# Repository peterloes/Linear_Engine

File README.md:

# Linear Actuator

A standalone Platform for Animal Manipulation 

This is the firmware for the LinearA_2017 (linear servo, i.e. stepper motor with spindle)
and project Servo_2015 (standard PWM servo).
Setup and control of the Actuator is done
via 3 keys, and, for selecting the two end positions, also via two external
inputs, please see below.  The firmware supports soft-start, i.e. the Actuator
speed will be ramped-up during the start phase.

Supported:
- Nanotec SMC11-2 Leistungsendstufe
- Nanotec Linear Aktuator L2018S0604-T3,5x1

The linear setup procedure consists of 4 steps:
- Adjust end position 1.  A linear actuator
  doesn't know about its absolute position, therefore it first moves to
  to its physical start position (near the motor) after power-up.  From
  that, position 1 can be adjusted.
- Adjust end position 2.  This is the opposite end position to position 1.
- Adjust actuator speed.  The actuator permanently moves between the two end
  points.  The speed can be adjusted via S1 and S2.
- Asserting S3 the 4th time stores the servo parameters into FLASH and
  returns to normal operation.

Prototype: Feeder

https://github.com/peterloes/Linear_Engine/blob/master/Getting_Started_Tutorial/1_poster_overview.pdf

Mainboard:

https://github.com/peterloes/MOMO

Manufacture:

https://github.com/peterloes/Linear_Engine/blob/master/Getting_Started_Tutorial/3_Supplier.txt

The standalone Linear Actuator features EFM32 ...the world´s most energy friendly microcontrollers

ARM Cortex-M3 EFM32G230F128

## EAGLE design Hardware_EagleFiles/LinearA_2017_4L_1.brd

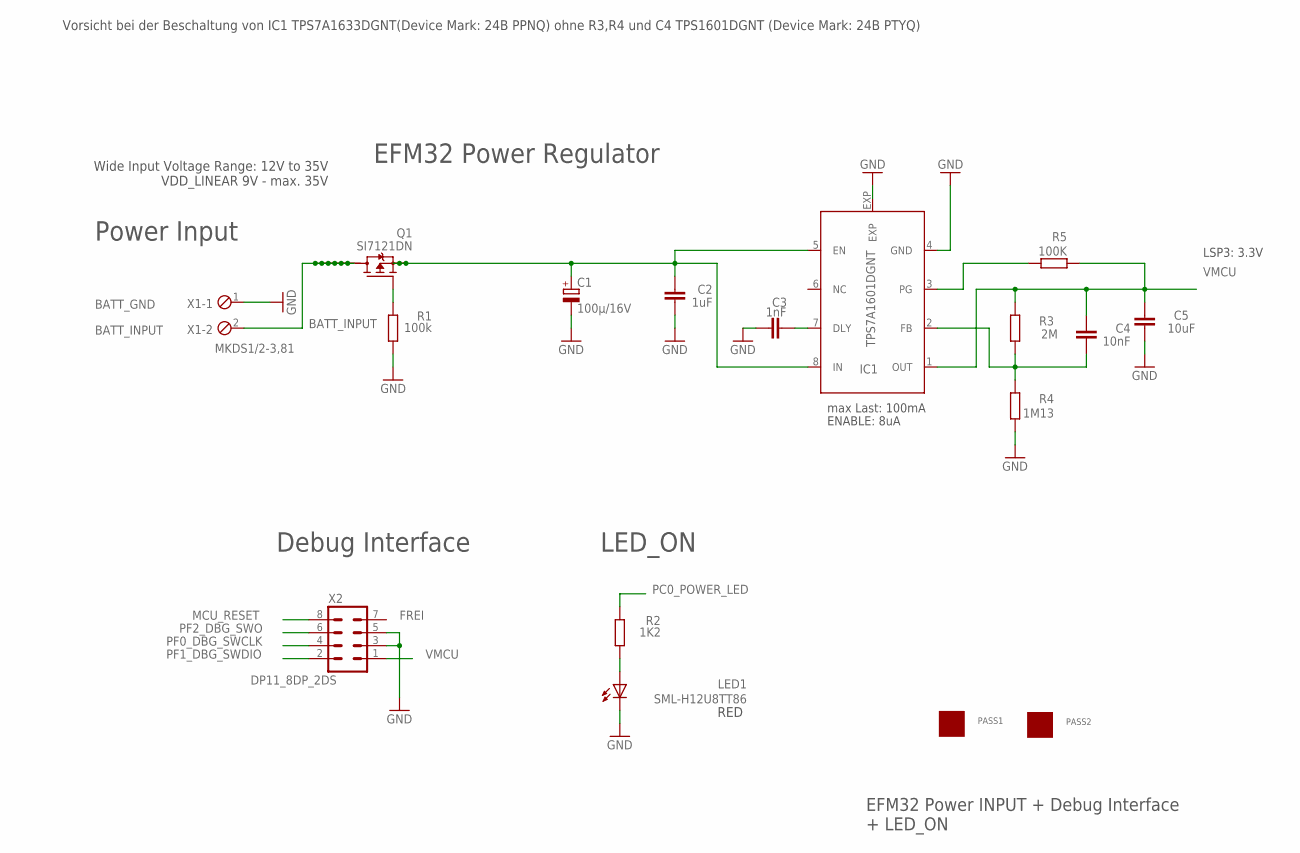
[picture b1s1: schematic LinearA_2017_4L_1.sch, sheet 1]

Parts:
C1: 100µ/16V; PANASONIC_E
C2: 1uF; C0603
C3: 1nF; C0603
C4: 10nF; C0603
C5: 10uF; C1206
IC1: TPS7A1601DGNT; DGN_S-PDSO-G8-EXP
LED1: SML-H12U8TT86; CHIPLED_0805
PASS1, PASS2: ROUND_1MM1.5; ROUND2_1.5MM
Q1: SI7121DN; TRANSISTOR-FET_1212-8S
R1: 100k; R0805
R2: 1K2; R0805
R3: 2M; R0805
R4: 1M13; R0805
R5: 100K; R0805
X1: MKDS1/2-3,81; 2POL381
X2: DP11_8DP_2DS; DP11_8DP-2DS

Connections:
BATT_INPUT: Q1.5 (D), Q1.6 (D), Q1.7 (D), Q1.8 (D), Q1.9 (D), Q1.10 (D), Q1.11 (D), X1.2; also elsewhere on the board
GND: C1.-, C2.1, C3.1, C5.1, IC1.4 (GND), IC1.EXP, LED1.C, R1.1, R4.1, X1.1, X2.3, X2.5; also elsewhere on the board
MCU_RESET: X2.8; also elsewhere on the board
unnamed: C1.+, C2.2, IC1.5 (EN), IC1.8 (IN), Q1.1 (S), Q1.2 (S), Q1.3 (S)
unnamed: C3.2, IC1.7 (DLY)
unnamed: C4.1, IC1.2 (FB), R3.1, R4.2
unnamed: IC1.3 (PG), R5.2
unnamed: Q1.4 (G), R1.2
unnamed: LED1.A, R2.2
PC0_POWER_LED: R2.1; also elsewhere on the board
PF0_DBG_SWCLK: X2.4; also elsewhere on the board
PF1_DBG_SWDIO: X2.2; also elsewhere on the board
PF2_DBG_SWO: X2.6; also elsewhere on the board
VMCU: C4.2, C5.2, IC1.1 (OUT), R3.2, R5.1, X2.1; also elsewhere on the board

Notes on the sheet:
BATT_GND
Wide Input Voltage Range: 12V to 35V VDD_LINEAR 9V - max. 35V
BATT_INPUT
EFM32 Power INPUT + Debug Interface + LED_ON
ENABLE: 8uA
Power Input
max Last: 100mA
LSP3: 3.3V
EFM32 Power Regulator
Debug Interface
LED_ON
FREI
Vorsicht bei der Beschaltung von IC1 TPS7A1633DGNT(Device Mark: 24B PPNQ) ohne R3,R4 und C4 TPS1601DGNT (Device Mark: 24B PTYQ)
RED

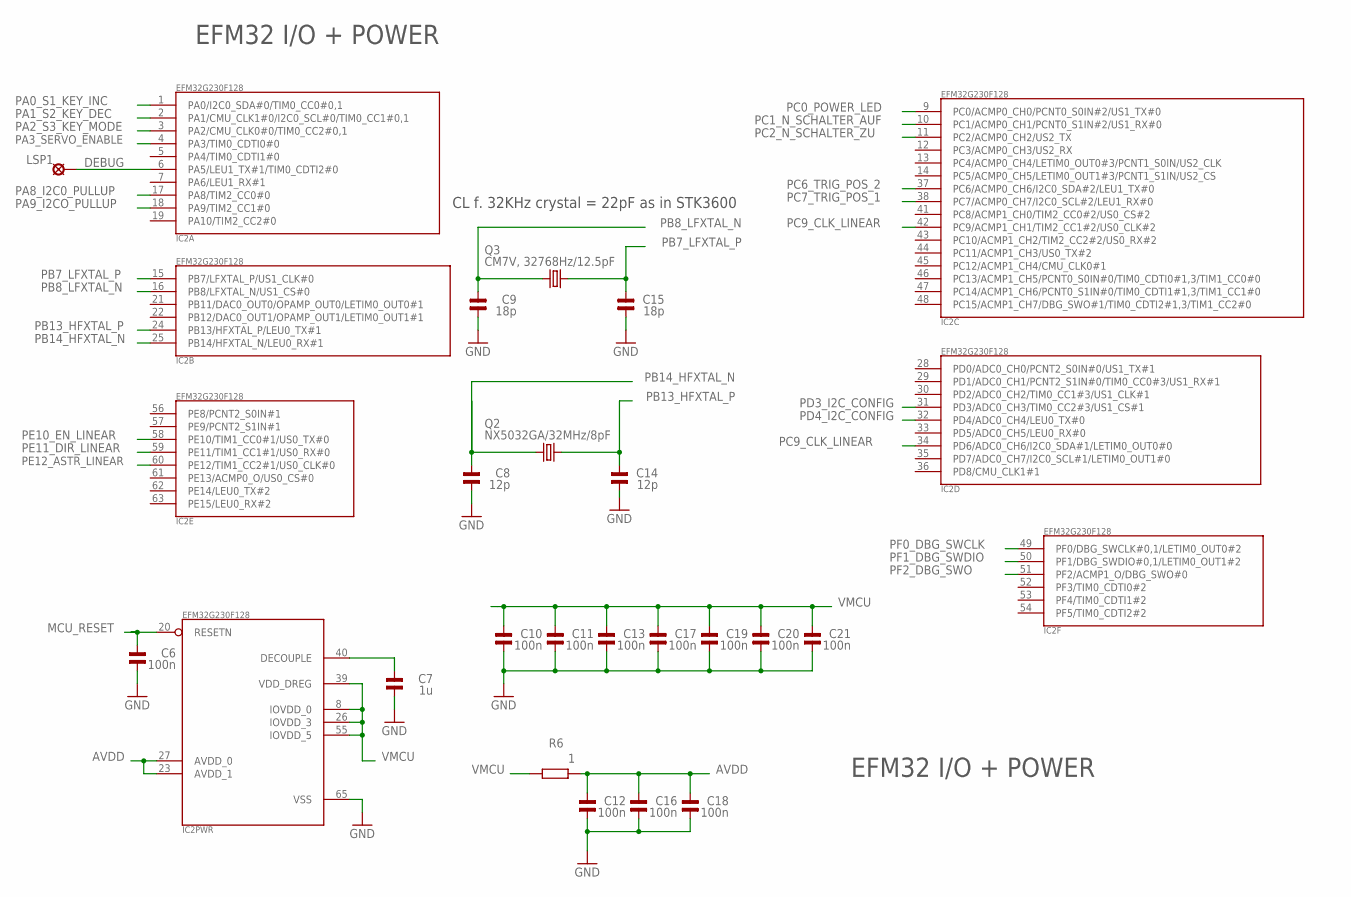
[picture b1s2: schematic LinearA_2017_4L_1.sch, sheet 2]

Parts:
C6, C10, C11, C12, C13, C16, C17, C18, C19, C20, C21: 100n; 0805
C7: 1u; 0805
C8, C14: 12p; 0805
C9, C15: 18p; 0805
IC2: EFM32G230F128; QFN64
LSP1: (n.b.)LSP10; LSP10
Q2: NX5032GA/32MHz/8pF; CRYSTAL2P5.0X3.2
Q3: CM7V, 32768Hz/12.5pF; CRYSTAL2P3.2X1.5
R6: 1; R0805

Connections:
AVDD: C12.2, C16.2, C18.2, IC2.23 (AVDD_1), IC2.27 (AVDD_0), R6.2
DEBUG: IC2.6 (PA5/LEU1_TX#1/TIM0_CDTI2#0), LSP1.MP
GND: C6.1, C7.1, C8.1, C9.1, C10.1, C11.1, C12.1, C13.1, C14.1, C15.1, C16.1, C17.1, C18.1, C19.1, C20.1, C21.1, IC2.65 (VSS); also elsewhere on the board
MCU_RESET: C6.2, IC2.20 (RESETN); also elsewhere on the board
unnamed: C7.2, IC2.40 (DECOUPLE)
PA0_S1_KEY_INC: IC2.1 (PA0/I2C0_SDA#0/TIM0_CC0#0,1); also elsewhere on the board
PA1_S2_KEY_DEC: IC2.2 (PA1/CMU_CLK1#0/I2C0_SCL#0/TIM0_CC1#0,1); also elsewhere on the board
PA2_S3_KEY_MODE: IC2.3 (PA2/CMU_CLK0#0/TIM0_CC2#0,1); also elsewhere on the board
PA3_SERVO_ENABLE: IC2.4 (PA3/TIM0_CDTI0#0); also elsewhere on the board
PA8_I2C0_PULLUP: IC2.17 (PA8/TIM2_CC0#0); also elsewhere on the board
PA9_I2CO_PULLUP: IC2.18 (PA9/TIM2_CC1#0); also elsewhere on the board
PB7_LFXTAL_P: C15.2, IC2.15 (PB7/LFXTAL_P/US1_CLK#0), Q3.2
PB8_LFXTAL_N: C9.2, IC2.16 (PB8/LFXTAL_N/US1_CS#0), Q3.1
PB13_HFXTAL_P: C14.2, IC2.24 (PB13/HFXTAL_P/LEU0_TX#1), Q2.2
PB14_HFXTAL_N: C8.2, IC2.25 (PB14/HFXTAL_N/LEU0_RX#1), Q2.1
PC0_POWER_LED: IC2.9 (PC0/ACMP0_CH0/PCNT0_S0IN#2/US1_TX#0); also elsewhere on the board
PC1_N_SCHALTER_AUF: IC2.10 (PC1/ACMP0_CH1/PCNT0_S1IN#2/US1_RX#0); also elsewhere on the board
PC2_N_SCHALTER_ZU: IC2.11 (PC2/ACMP0_CH2/US2_TX); also elsewhere on the board
PC6_TRIG_POS_2: IC2.37 (PC6/ACMP0_CH6/I2C0_SDA#2/LEU1_TX#0); also elsewhere on the board
PC7_TRIG_POS_1: IC2.38 (PC7/ACMP0_CH7/I2C0_SCL#2/LEU1_RX#0); also elsewhere on the board
PC9_CLK_LINEAR: IC2.34 (PD6/ADC0_CH6/I2C0_SDA#1/LETIM0_OUT0#0), IC2.42 (PC9/ACMP1_CH1/TIM2_CC1#2/US0_CLK#2); also elsewhere on the board
PD3_I2C_CONFIG: IC2.31 (PD3/ADC0_CH3/TIM0_CC2#3/US1_CS#1); also elsewhere on the board
PD4_I2C_CONFIG: IC2.32 (PD4/ADC0_CH4/LEU0_TX#0); also elsewhere on the board
PE10_EN_LINEAR: IC2.58 (PE10/TIM1_CC0#1/US0_TX#0); also elsewhere on the board
PE11_DIR_LINEAR: IC2.59 (PE11/TIM1_CC1#1/US0_RX#0); also elsewhere on the board
PE12_ASTR_LINEAR: IC2.60 (PE12/TIM1_CC2#1/US0_CLK#0); also elsewhere on the board
PF0_DBG_SWCLK: IC2.49 (PF0/DBG_SWCLK#0,1/LETIM0_OUT0#2); also elsewhere on the board
PF1_DBG_SWDIO: IC2.50 (PF1/DBG_SWDIO#0,1/LETIM0_OUT1#2); also elsewhere on the board
PF2_DBG_SWO: IC2.51 (PF2/ACMP1_O/DBG_SWO#0); also elsewhere on the board
VMCU: C10.2, C11.2, C13.2, C17.2, C19.2, C20.2, C21.2, IC2.8 (IOVDD_0), IC2.26 (IOVDD_3), IC2.39 (VDD_DREG), IC2.55 (IOVDD_5), R6.1; also elsewhere on the board

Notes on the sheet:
EFM32 I/O + POWER
CL f. 32KHz crystal = 22pF as in STK3600

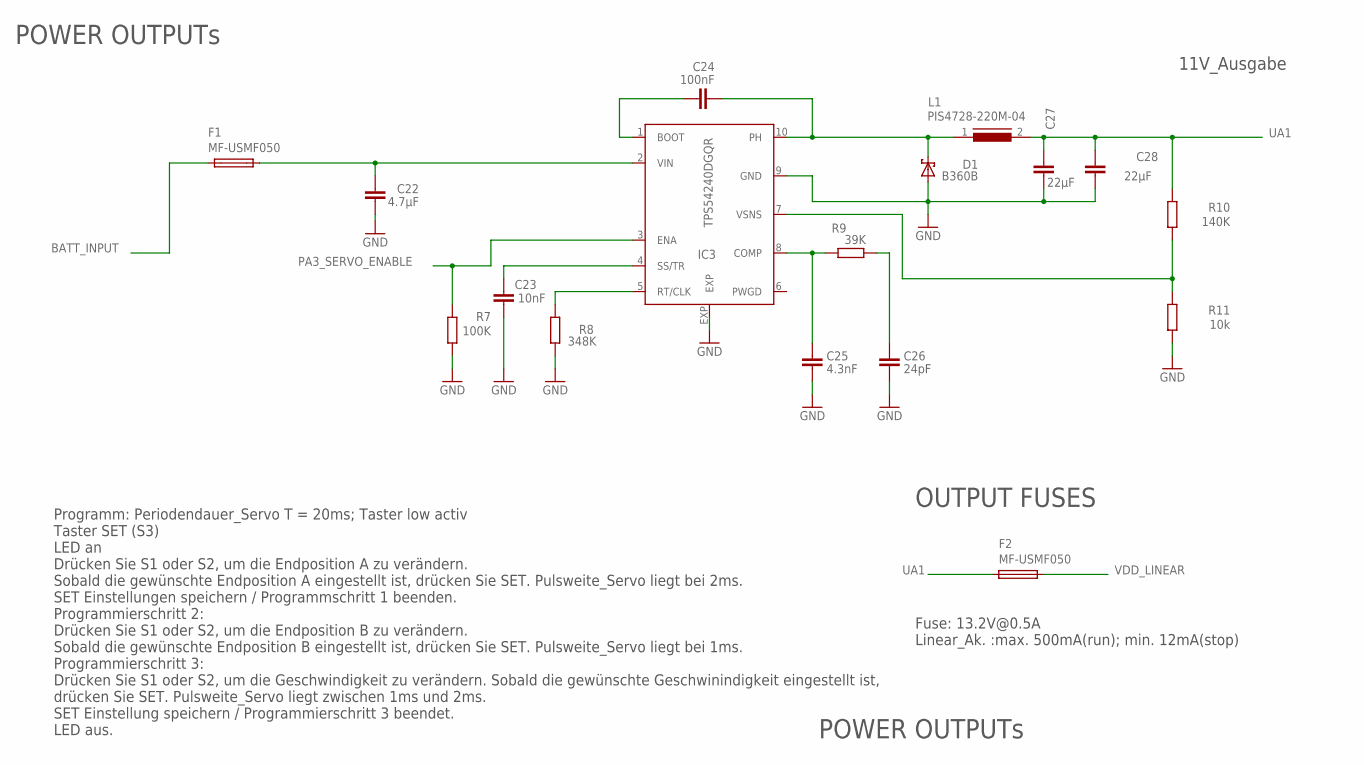
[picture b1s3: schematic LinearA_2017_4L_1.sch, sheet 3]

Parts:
C22: 4.7µF; C1210
C23: 10nF; C0603
C24: 100nF; C0603
C25: 4.3nF; C0603
C26: 24pF; C0603
C27, C28: 22µF; C1210
D1: B360B; SMB
F1, F2: MF-USMF050; PFUF_1210POLY
IC3: TPS54240DGQR; S-PDSO-G10
L1: PIS4728-220M-04; DR127
R7: 100K; R0805
R8: 348K; R0805
R9: 39K; R0805
R10: 140K; R0805
R11: 10k; R0805

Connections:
BATT_INPUT: F1.P$1 (1); also elsewhere on the board
GND: C22.2, C23.2, C25.2, C26.2, C27.2, C28.2, D1.A, IC3.9 (GND), IC3.EXP, R7.1, R8.1, R11.1; also elsewhere on the board
unnamed: IC3.5 (RT/CLK), R8.2
unnamed: C24.2, IC3.1 (BOOT)
unnamed: C24.1, D1.C, IC3.10 (PH), L1.1
unnamed: C23.1, IC3.4 (SS/TR)
unnamed: C25.1, IC3.8 (COMP), R9.1
unnamed: C26.1, R9.2
unnamed: IC3.7 (VSNS), R10.1, R11.2
unnamed: C22.1, F1.P$2 (2), IC3.2 (VIN)
PA3_SERVO_ENABLE: IC3.3 (ENA), R7.2; also elsewhere on the board
UA1: C27.1, C28.1, F2.P$1 (1), L1.2, R10.2
VDD_LINEAR: F2.P$2 (2); also elsewhere on the board

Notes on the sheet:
11V_Ausgabe
POWER OUTPUTs
OUTPUT FUSES
Programm: Periodendauer_Servo T = 20ms; Taster low activ Taster SET (S3) LED an Drücken Sie S1 oder S2, um die Endposition A zu verändern. Sobald die gewünschte Endposition A eingestellt ist, drücken Sie SET. Pulsweite_Servo liegt bei 2ms. SET Einstellungen speichern / Programmschritt 1 beenden. Pr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
Fuse: 13.2V@0.5A Linear_Ak. :max. 500mA(run); min. 12mA(stop)

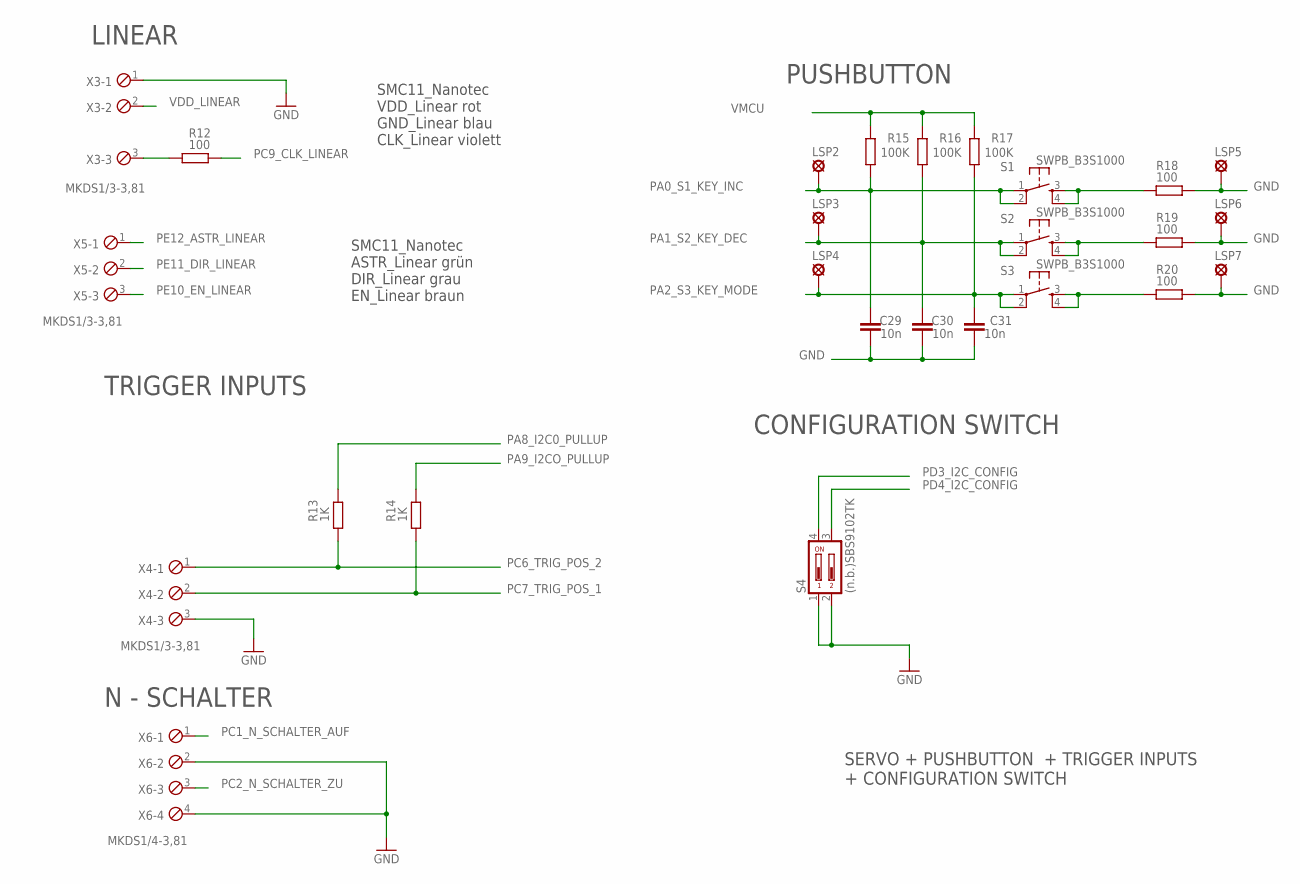
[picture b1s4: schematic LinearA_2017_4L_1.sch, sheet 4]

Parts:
C29, C30, C31: 10n; C0603
LSP2, LSP3, LSP4, LSP5, LSP6, LSP7: (n.b.)LSP10; LSP10
R12, R18, R19, R20: 100; R0805
R13, R14: 1K; R0805
R15, R16, R17: 100K; R0805
S1, S2, S3: SWPB_B3S1000; DTSM-6
S4: (n.b.)SBS9102TK; CTS-219-02
X3, X4, X5: MKDS1/3-3,81; 3POL381
X6: MKDS1/4-3,81; 4POL381

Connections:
GND: C29.1, C30.1, C31.1, LSP5.MP, LSP6.MP, LSP7.MP, R18.2, R19.2, R20.2, S4.1, S4.2, X3.1, X4.3, X6.2, X6.4; also elsewhere on the board
unnamed: R12.1, X3.3
unnamed: R20.1, S3.3, S3.4
unnamed: R18.1, S1.3, S1.4
unnamed: R19.1, S2.3, S2.4
PA0_S1_KEY_INC: C29.2, LSP2.MP, R15.1, S1.1, S1.2; also elsewhere on the board
PA1_S2_KEY_DEC: C30.2, LSP3.MP, R16.1, S2.1, S2.2; also elsewhere on the board
PA2_S3_KEY_MODE: C31.2, LSP4.MP, R17.1, S3.1, S3.2; also elsewhere on the board
PA8_I2C0_PULLUP: R13.2; also elsewhere on the board
PA9_I2CO_PULLUP: R14.2; also elsewhere on the board
PC1_N_SCHALTER_AUF: X6.1; also elsewhere on the board
PC2_N_SCHALTER_ZU: X6.3; also elsewhere on the board
PC6_TRIG_POS_2: R13.1, X4.1; also elsewhere on the board
PC7_TRIG_POS_1: R14.1, X4.2; also elsewhere on the board
PC9_CLK_LINEAR: R12.2; also elsewhere on the board
PD3_I2C_CONFIG: S4.4; also elsewhere on the board
PD4_I2C_CONFIG: S4.3; also elsewhere on the board
PE10_EN_LINEAR: X5.3; also elsewhere on the board
PE11_DIR_LINEAR: X5.2; also elsewhere on the board
PE12_ASTR_LINEAR: X5.1; also elsewhere on the board
VDD_LINEAR: X3.2; also elsewhere on the board
VMCU: R15.2, R16.2, R17.2; also elsewhere on the board

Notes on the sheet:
SERVO + PUSHBUTTON + TRIGGER INPUTS + CONFIGURATION SWITCH
LINEAR
SMC11_Nanotec VDD_Linear rot GND_Linear blau CLK_Linear violett
TRIGGER INPUTS
PUSHBUTTON
CONFIGURATION SWITCH
SMC11_Nanotec ASTR_Linear grün DIR_Linear grau EN_Linear braun
N - SCHALTER

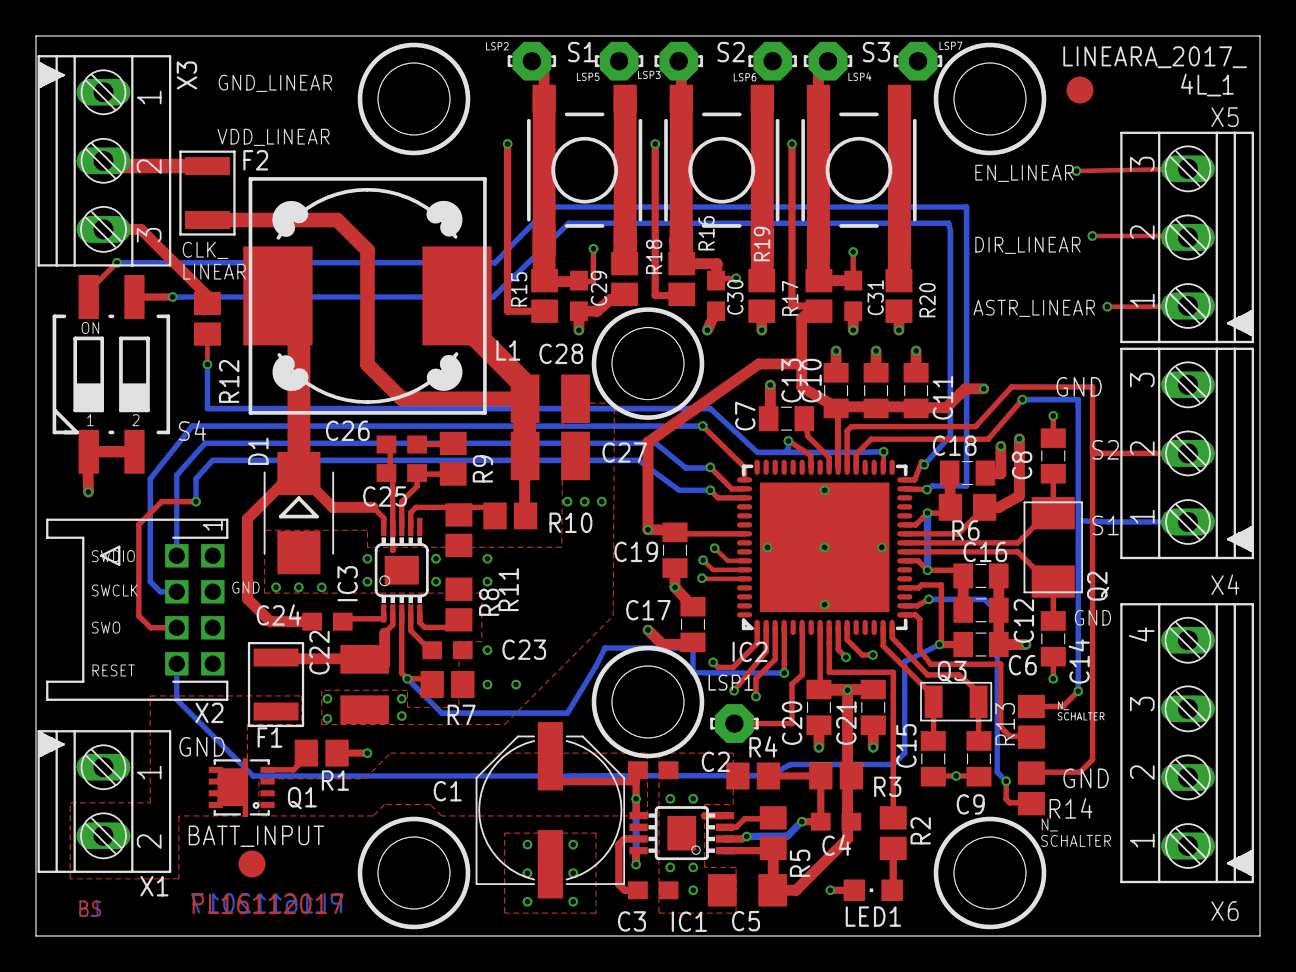
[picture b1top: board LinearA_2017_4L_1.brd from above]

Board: 4 copper layers, 68.0 x 50.0 mm, 81 parts (0 on the bottom side), 51 nets.

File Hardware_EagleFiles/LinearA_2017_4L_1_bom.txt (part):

Part  Value                Device                  Package                Description                                                    MF MPN OC_FARNELL OC_NEWARK
C1    100µ/16V             CPOL-EUE                PANASONIC_E            POLARIZED CAPACITOR, European symbol                                                      
C2    1uF                  C-EUC0603               C0603                  CAPACITOR, European symbol                                                                
C3    1nF                  C-EUC0603               C0603                  CAPACITOR, European symbol                                                                
C4    10nF                 C-EUC0603               C0603                  CAPACITOR, European symbol                                                                
C5    10uF                 C-EUC1206               C1206                  CAPACITOR, European symbol                                                                
C6    100n                 C_SMD0805               0805                                                                                                             
C7    1u                   C_SMD0805               0805                                                                                                             
C8    12p                  C_SMD0805               0805                                                                                                             
C9    18p                  C_SMD0805               0805                                                                                                             
C10   100n                 C_SMD0805               0805                                                                                                             
C11   100n                 C_SMD0805               0805                                                                                                             
C12   100n                 C_SMD0805               0805                                                                                                             
C13   100n                 C_SMD0805               0805                                                                                                             
C14   12p                  C_SMD0805               0805                                                                                                             
C15   18p                  C_SMD0805               0805                                                                                                             
C16   100n                 C_SMD0805               0805                                                                                                             
C17   100n                 C_SMD0805               0805                                                                                                             
C18   100n                 C_SMD0805               0805                                                                                                             
C19   100n                 C_SMD0805               0805                                                                                                             
C20   100n                 C_SMD0805               0805                                                                                                             
C21   100n                 C_SMD0805               0805                                                                                                             
C22   4.7µF                C-EUC1210               C1210                  CAPACITOR, European symbol                                                                
C23   10nF                 C-EUC0603               C0603                  CAPACITOR, European symbol                                                                
C24   100nF                C-EUC0603               C0603                  CAPACITOR, European symbol                                                                
C25   4.3nF                C-EUC0603               C0603                  CAPACITOR, European symbol                                                                
C26   24pF                 C-EUC0603               C0603                  CAPACITOR, European symbol                                                                
C27   22µF                 C-EUC1210               C1210                  CAPACITOR, European symbol                                                                
C28   22µF                 C-EUC1210               C1210                  CAPACITOR, European symbol                                                                
C29   10n                  C-EUC0603               C0603                  CAPACITOR, European symbol                                                                
C30   10n                  C-EUC0603               C0603                  CAPACITOR, European symbol                                                                
C31   10n                  C-EUC0603               C0603                  CAPACITOR, European symbol                                                                
D1    B360B                SCHOTTKY-DIODESMD       SMB                    Schottky Diode                                                                            
F1    MF-USMF050           PFUF                    PFUF_1210POLY                                                                                                    
F2    MF-USMF050           PFUF                    PFUF_1210POLY                                                                                                    
IC1   TPS7A1601DGNT        TPS7A16                 DGN_S-PDSO-G8-EXP                                                                                                
IC2   EFM32G230F128        EFM32G230F128           QFN64                  EFM32G230F128 Gecko Microcontroller in 9mm x 9mm QFN64 package                            
IC3   TPS54240DGQR         TPS54240DGQR            S-PDSO-G10                                                                                                       
L1    PIS4728-220M-04      DR127                   DR127                  High Power Density, High Efficiency, Shielded Inductors                                   
LED1  SML-H12U8TT86        LEDCHIPLED_0805         CHIPLED_0805           LED                                                                                       
LSP1  (n.b.)LSP10          LSP10                   LSP10                  SOLDER PAD drill 1.0 mm, distributor Buerklin, 12H555                                     
LSP2  (n.b.)LSP10          LSP10                   LSP10                  SOLDER PAD drill 1.0 mm, distributor Buerklin, 12H555                                     
LSP3  (n.b.)LSP10          LSP10                   LSP10                  SOLDER PAD drill 1.0 mm, distributor Buerklin, 12H555                                     
LSP4  (n.b.)LSP10          LSP10                   LSP10                  SOLDER PAD drill 1.0 mm, distributor Buerklin, 12H555                                     
LSP5  (n.b.)LSP10          LSP10                   LSP10                  SOLDER PAD drill 1.0 mm, distributor Buerklin, 12H555                                     
LSP6  (n.b.)LSP10          LSP10                   LSP10                  SOLDER PAD drill 1.0 mm, distributor Buerklin, 12H555                                     
LSP7  (n.b.)LSP10          LSP10                   LSP10                  SOLDER PAD drill 1.0 mm, distributor Buerklin, 12H555                                     
PASS1 ROUND_1MM1.5         ROUND_1MM1.5            ROUND2_1.5MM                                                                                                     
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

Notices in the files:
parts and their libraries:
EnergyMicro: CC0 License
SparkFun-Aesthetics: Licensing: CC v3.0 Share-Alike You are welcome to use this library for commercial purposes.
